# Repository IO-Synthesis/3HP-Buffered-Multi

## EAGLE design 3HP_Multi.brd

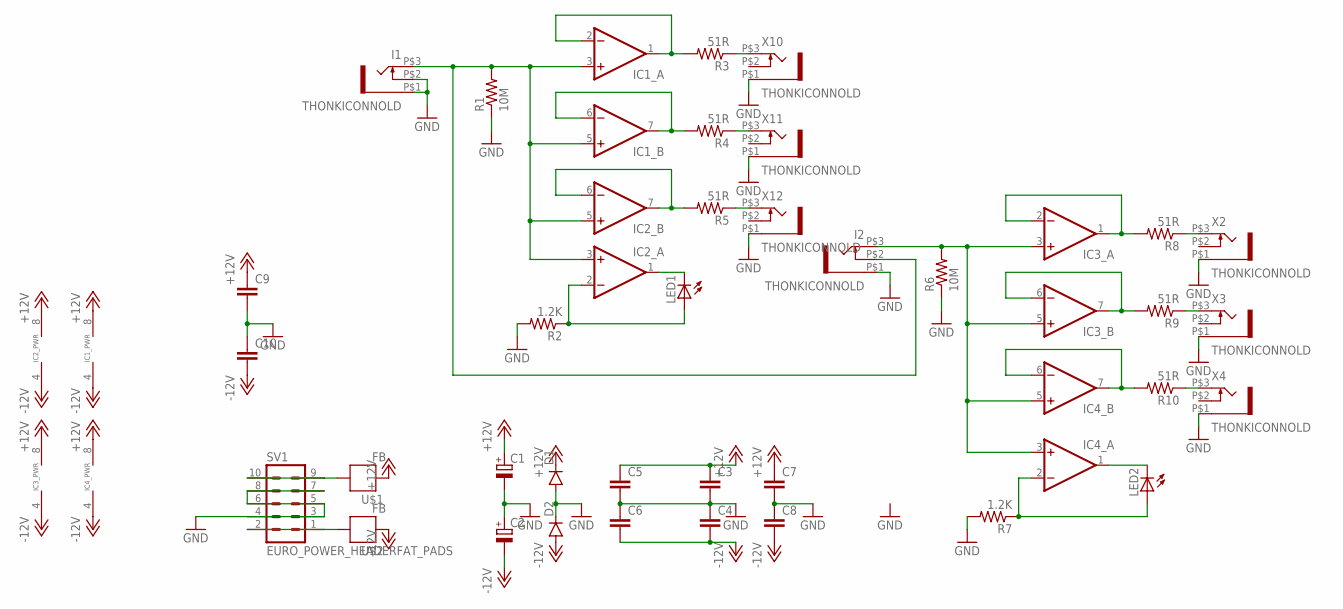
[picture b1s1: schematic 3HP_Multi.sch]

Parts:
C1, C2: CAPACITOR_POL-CASE_B; CASE_B
C3, C4, C5, C6, C7, C8, C9, C10: CAP0603-CAP; 0603-CAP
D1, D2: DIODESOD123; SOD-123
I1, I2: THONKICONNOLD; THONKICONN
IC1, IC2, IC3, IC4: DUALSMD; SO08
LED1, LED2: LED3MM
R1, R6: 10M; 0603-RES
R2, R7: 1.2K; 0603-RES
R3, R4, R5, R8, R9, R10: 51R; 0603-RES
SV1: EURO_POWER_HEADERFAT_PADS; EURO_PWR_HEADER_FAT
U$1, U$2: FB; 0603
X2, X3, X4, X10, X11, X12: THONKICONNOLD; THONKICONN

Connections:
+12V: C1.+, C3.1, C5.1, C7.1, C9.1, D1.C, IC1.8 (V+), IC2.8 (V+), IC3.8 (V+), IC4.8 (V+), U$1.2
-12V: C2.-, C4.2, C6.2, C8.2, C10.2, D2.A, IC1.4 (V-), IC2.4 (V-), IC3.4 (V-), IC4.4 (V-), U$2.2
GND: C1.-, C2.+, C3.2, C4.1, C5.2, C6.1, C7.2, C8.1, C9.2, C10.1, D1.A, D2.C, I1.P$1 (5), I1.P$2 (4), I2.P$1 (5), R1.1, R2.2, R6.1, R7.2, SV1.3, SV1.4, SV1.5, SV1.6, SV1.7, SV1.8, X2.P$1 (5), X3.P$1 (5), X4.P$1 (5), X10.P$1 (5), X11.P$1 (5), X12.P$1 (5)
unnamed: IC4.1 (OUT), LED2.K (C)
unnamed: IC1.6 (-IN), IC1.7 (OUT), R4.2
unnamed: IC1.1 (OUT), IC1.2 (-IN), R3.2
unnamed: IC2.1 (OUT), LED1.K (C)
unnamed: IC2.6 (-IN), IC2.7 (OUT), R5.2
unnamed: R5.1, X12.P$3 (3)
unnamed: R4.1, X11.P$3 (3)
unnamed: R3.1, X10.P$3 (3)
unnamed: SV1.9, SV1.10, U$1.1
unnamed: R8.1, X2.P$3 (3)
unnamed: IC3.1 (OUT), IC3.2 (-IN), R8.2
unnamed: R9.1, X3.P$3 (3)
unnamed: IC2.2 (-IN), LED1.A, R2.1
unnamed: I1.P$3 (3), I2.P$2 (4), IC1.3 (+IN), IC1.5 (+IN), IC2.3 (+IN), IC2.5 (+IN), R1.2
unnamed: IC3.6 (-IN), IC3.7 (OUT), R9.2
unnamed: R10.1, X4.P$3 (3)
unnamed: IC4.6 (-IN), IC4.7 (OUT), R10.2
unnamed: IC4.2 (-IN), LED2.A, R7.1
unnamed: I2.P$3 (3), IC3.3 (+IN), IC3.5 (+IN), IC4.3 (+IN), IC4.5 (+IN), R6.2
unnamed: SV1.1, SV1.2, U$2.1

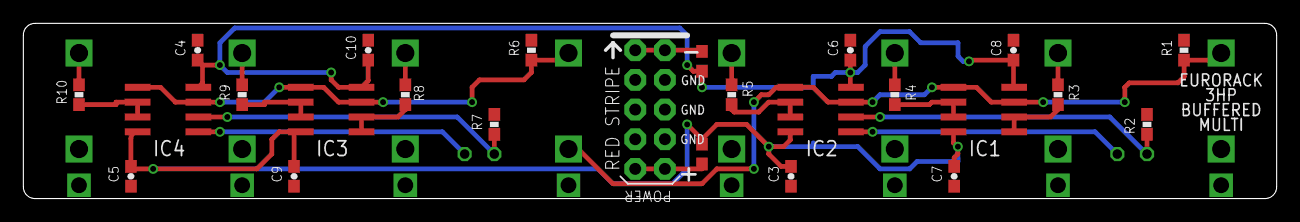
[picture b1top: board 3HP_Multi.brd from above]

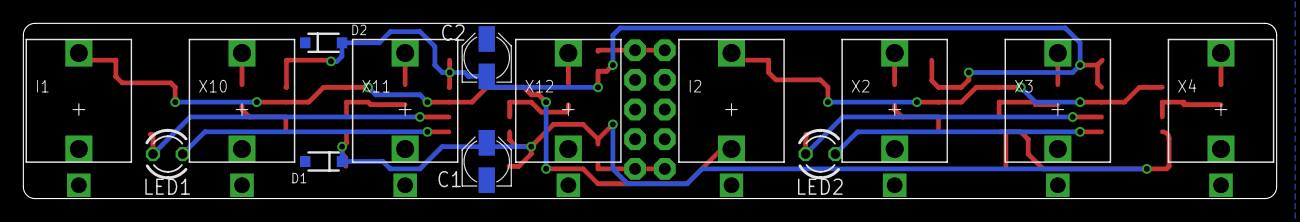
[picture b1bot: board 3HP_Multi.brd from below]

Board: 2 copper layers, 107.3 x 15.0 mm, 39 parts (14 on the bottom side), 23 nets.

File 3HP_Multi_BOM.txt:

3HP_Multi_BOM

Qty Value                     Device                    Parts
8   100nF                     CAP0603-CAP               C3, C4, C5, C6, C7, C8, C9, C10
2   10uF                      CAPACITOR_POL-CASE_B      C1, C2                           
2                             DIODESOD123               D1, D2
4                             DUALSMD                   IC1, IC2, IC3, IC4
2                             Dual_Color_LED3MM         LED1, LED2
2   1.2K                      RESISTOR0603              R2, R7
2   10M                       RESISTOR0603              R1, R6
6   51R                       RESISTOR0603              R3, R4, R5, R8, R9, R10
1   EURO_POWER_HEADERFAT_PADS EURO_POWER_HEADERFAT_PADS SV1
2   FB                        FB                        U$1, U$2
8   THONKICONNOLD             THONKICONNOLD             I1, I2, X2, X3, X4, X10, X11, X12

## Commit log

2016-01-18 :tada: Added .gitattributes & .gitignore files
2016-01-18 3HP Eurorack Buffered Multi

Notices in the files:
parts and their libraries:
SparkFun-Passives: Licensing: Creative Commons ShareAlike 4.0 International - https://creativecommons.org/licenses/by-sa/4.0
